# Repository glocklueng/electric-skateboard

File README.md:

electric-skateboard
===================

Hardware and a start to software for an electric skateboard. 

- v1 had some issues but was built and tested. 

- v2 is in progress. Board layout done, ordered from OSH Park.

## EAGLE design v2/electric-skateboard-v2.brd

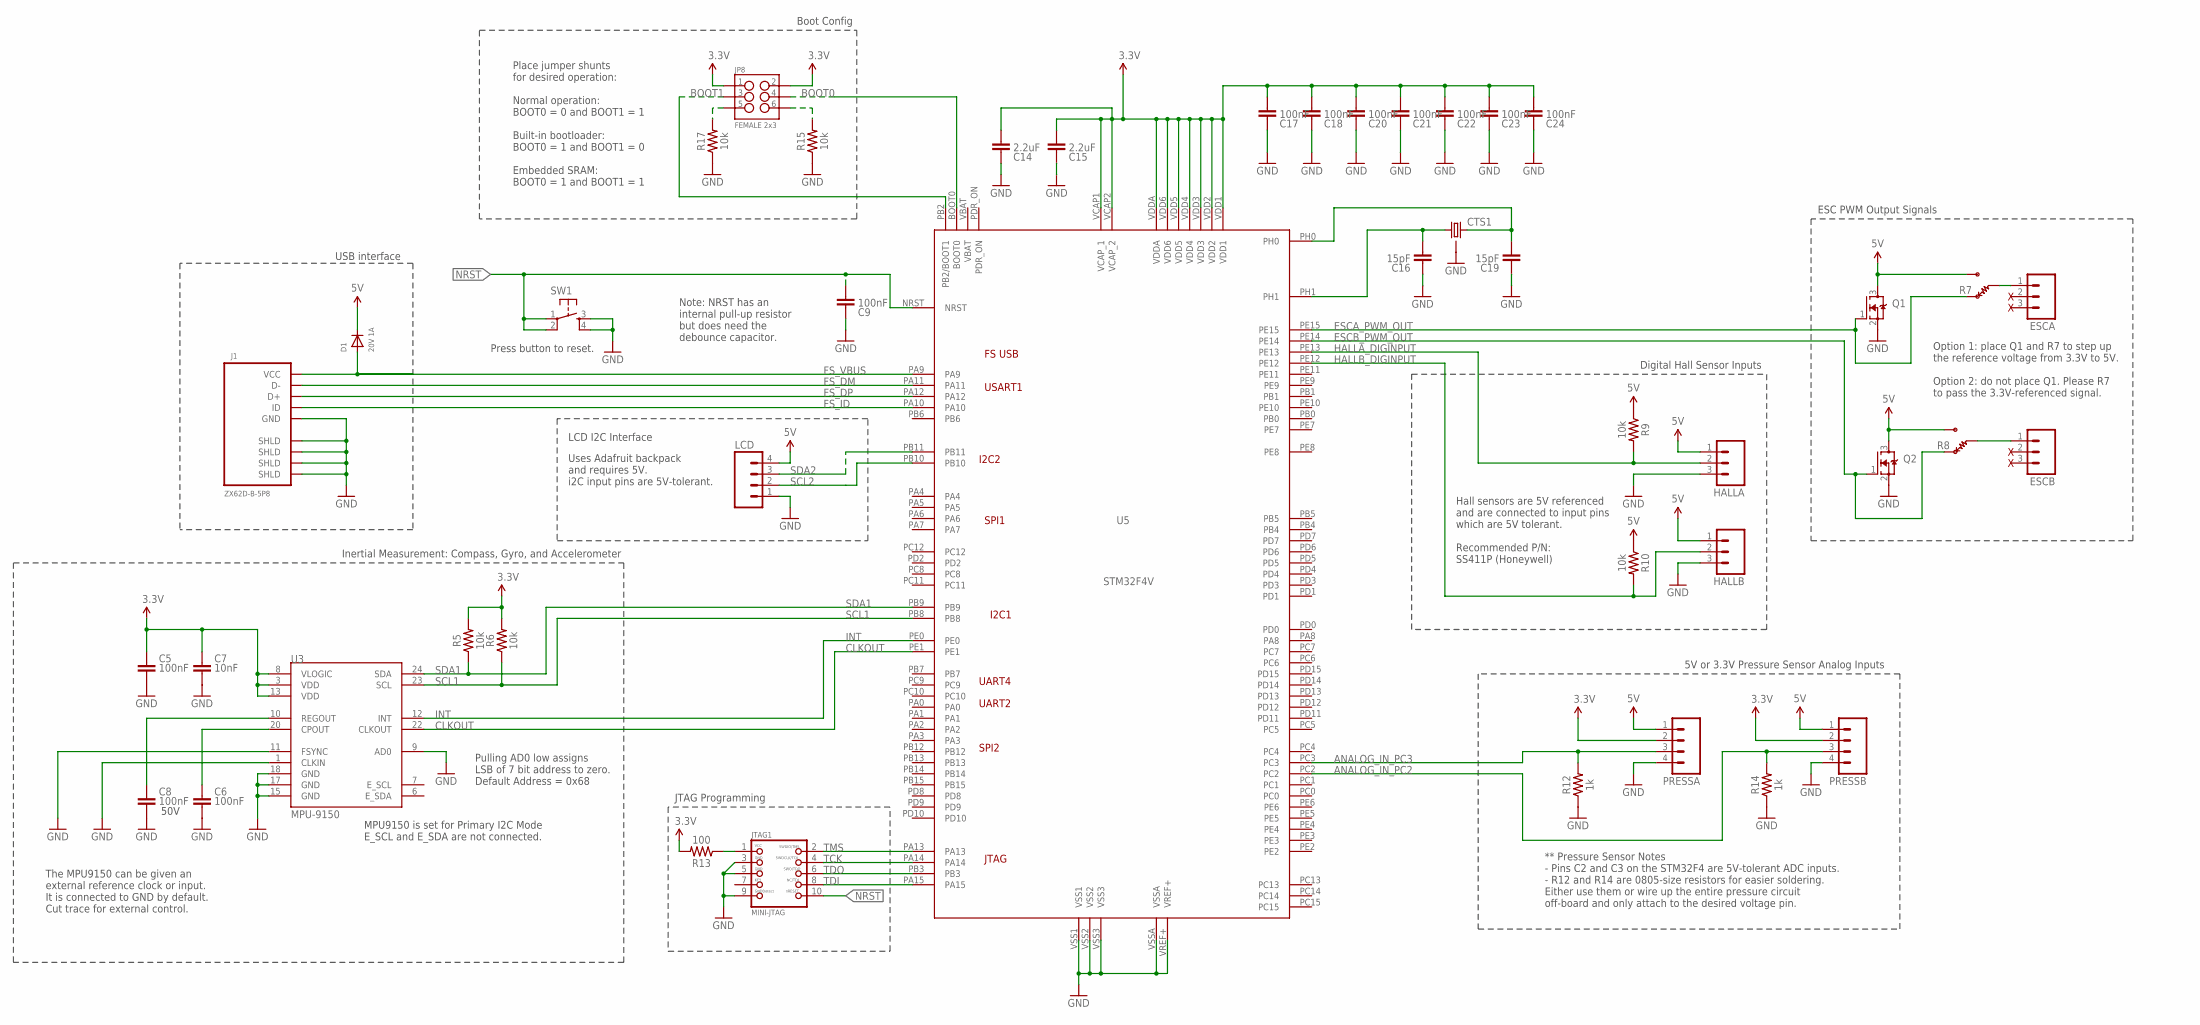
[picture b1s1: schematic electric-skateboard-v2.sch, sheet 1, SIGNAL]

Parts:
C5, C6, C8, C9, C17, C18, C20, C21, C22, C23, C24: 100nF; RLC-0402
C7: 10nF; RLC-0402
C14, C15: 2.2uF; RLC-0805
C16, C19: 15pF; RLC-0402
CTS1: CRYSTALCTS406; CTS406
D1: 20V 1A; SMADIODE
ESCA: M03LOCK_LONGPADS; 1X03_LOCK_LONGPADS
ESCB: M03LOCK_LONGPADS; 1X03_LOCK_LONGPADS
HALLA: M03LOCK_LONGPADS; 1X03_LOCK_LONGPADS
HALLB: M03LOCK_LONGPADS; 1X03_LOCK_LONGPADS
J1: ZX62D-B-5P8
JP8: FEMALE 2x3; 2X3
JTAG1: MINI-JTAG; MICROBUILDER_2X05_1.27MM_SMT
LCD: M04SCREW_LOCK; SCREWTERMINAL-3.5MM-4_LOCK
PRESSA: M04LOCK_LONGPADS; 1X04_LOCK_LONGPADS
PRESSB: M04LOCK_LONGPADS; 1X04_LOCK_LONGPADS
Q1, Q2: NTR4501N-D; SOT-23
R5, R6, R9, R10, R15, R17: 10k; RLC-0402
R7, R8: RES-OPTION; CAP-OPTION
R12, R14: 1k; RLC-0402
R13: 100; RLC-0402
SW1: TACTILE-SWITCH-PTH; TAC-SWITCH-PTH
U3: MPU-9150; QFN-24-NP
U5: STM32F4V; STM32F4_LQFP100

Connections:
3.3V: C5.1, C7.1, C14.2, C15.2, C17.2, C18.2, C20.2, C21.2, C22.2, C23.2, C24.2, JP8.1, JP8.2, PRESSA.2, PRESSB.2, R5.2, R6.2, R13.2, U3.3 (VDD), U3.8 (VLOGIC), U3.13 (VDD), U5.VCAP1 (VCAP_1), U5.VCAP2 (VCAP_2), U5.VDD1, U5.VDD2, U5.VDD3, U5.VDD4, U5.VDD5, U5.VDD6, U5.VDDA; also elsewhere on the board
5V: D1.C, HALLA.1, HALLB.1, LCD.4, PRESSA.1, PRESSB.1, Q1.3 (D), Q2.3 (D), R7.3, R8.3, R9.1, R10.1; also elsewhere on the board
ANALOG_IN_PC2: PRESSB.3, R14.2, U5.PC2
ANALOG_IN_PC3: PRESSA.3, R12.2, U5.PC3
BOOT0: JP8.4, U5.BOOT0
BOOT1: JP8.3, U5.PB2 (PB2/BOOT1)
CLKOUT: U3.22 (CLKOUT), U5.PE1
ESCA: ESCA.1, R7.2
ESCA_PWM_OUT: Q1.1 (G), R7.1, U5.PE15
ESCB: ESCB.1, R8.2
ESCB_PWM_OUT: Q2.1 (G), R8.1, U5.PE14
FS_DM: J1.P2 (D-), U5.PA11
FS_DP: J1.P3 (D+), U5.PA12
FS_ID: J1.P4 (ID), U5.PA10
FS_VBUS: D1.A, J1.P1 (VCC), U5.PA9
GND: C5.2, C6.2, C7.2, C8.2, C9.1, C14.1, C15.1, C16.1, C17.1, C18.1, C19.1, C20.1, C21.1, C22.1, C23.1, C24.1, CTS1.2 (GND), CTS1.4 (GND), HALLA.3, HALLB.3, J1.P5 (GND), J1.P$1 (SHLD), J1.P$2 (SHLD), J1.P$3 (SHLD), J1.P$4 (SHLD), JTAG1.3, JTAG1.5, JTAG1.9, LCD.1, PRESSA.4, PRESSB.4, Q1.2 (S), Q2.2 (S), R12.1, R14.1, R15.1, R17.1, SW1.3, SW1.4, U3.1 (CLKIN), U3.9 (AD0), U3.11 (FSYNC), U3.15 (GND), U3.17 (GND), U3.18 (GND), U5.VREF+, U5.VSS1, U5.VSS2, U5.VSS3, U5.VSSA; also elsewhere on the board
HALLA_DIGINPUT: HALLA.2, R9.2, U5.PE13
HALLB_DIGINPUT: HALLB.2, R10.2, U5.PE12
INT: U3.12 (INT), U5.PE0
unnamed: C6.1, U3.20 (CPOUT)
unnamed: JP8.6, R15.2
unnamed: JP8.5, R17.2
unnamed: C8.1, U3.10 (REGOUT)
unnamed: JTAG1.1, R13.1
NRST: C9.2, JTAG1.10, SW1.1, SW1.2, U5.NRST
OSC_IN1: C19.2, CTS1.3 (2), U5.PH0
OSC_OUT1: C16.2, CTS1.1, U5.PH1
SCL1: R6.1, U3.23 (SCL), U5.PB8
SCL2: LCD.2, U5.PB10
SDA1: R5.1, U3.24 (SDA), U5.PB9
SDA2: LCD.3, U5.PB11
TCK: JTAG1.4, U5.PA14
TDI: JTAG1.8, U5.PA15
TDO: JTAG1.6, U5.PB3
TMS: JTAG1.2, U5.PA13

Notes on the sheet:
50V
The MPU9150 can be given an external reference clock or input. It is connected to GND by default. Cut trace for external control.
Pulling AD0 low assigns LSB of 7 bit address to zero. Default Address = 0x68
MPU9150 is set for Primary I2C Mode E_SCL and E_SDA are not connected.
Option 1: place Q1 and R7 to step up the reference voltage from 3.3V to 5V. Option 2: do not place Q1. Please R7 to pass the 3.3V-referenced signal.
Hall sensors are 5V referenced and are connected to input pins which are 5V tolerant. Recommended P/N: SS411P (Honeywell)
** Pressure Sensor Notes - Pins C2 and C3 on the STM32F4 are 5V-tolerant ADC inputs. - R12 and R14 are 0805-size resistors for easier soldering. Either use them or wire up the entire pressure circuit off-board and only attach to the desired voltage pin.
ESC PWM Output Signals
Digital Hall Sensor Inputs
5V or 3.3V Pressure Sensor Analog Inputs
Inertial Measurement: Compass, Gyro, and Accelerometer
Note: NRST has an internal pull-up resistor but does need the debounce capacitor.
Place jumper shunts for desired operation: Normal operation: BOOT0 = 0 and BOOT1 = 1 Built-in bootloader: BOOT0 = 1 and BOOT1 = 0 Embedded SRAM: BOOT0 = 1 and BOOT1 = 1
Boot Config
Uses Adafruit backpack and requires 5V. i2C input pins are 5V-tolerant.
LCD I2C Interface
USB interface
JTAG Programming
Press button to reset.

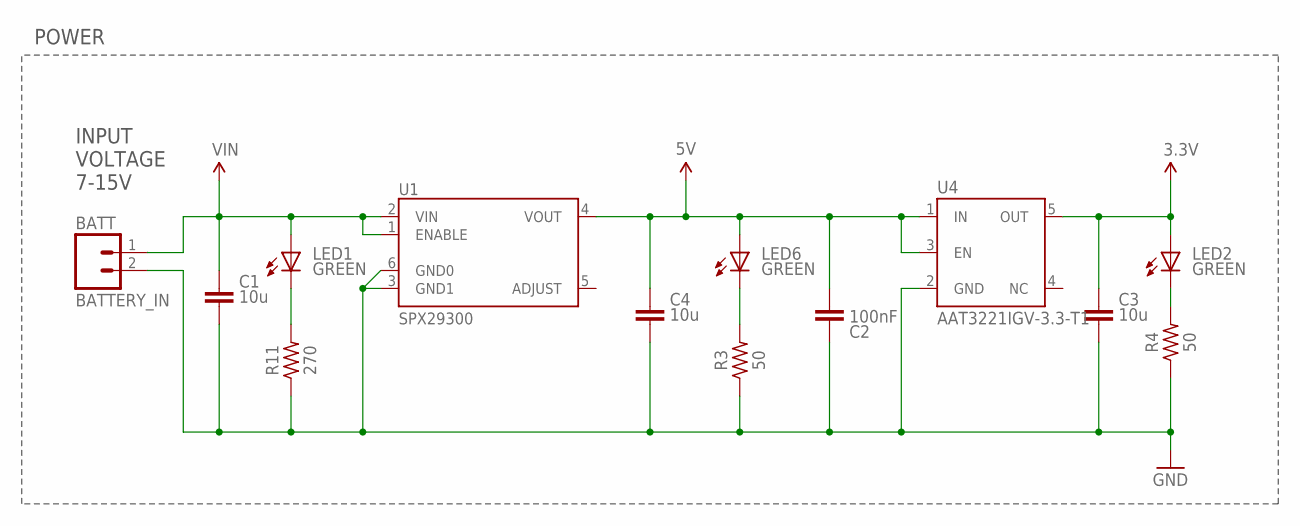
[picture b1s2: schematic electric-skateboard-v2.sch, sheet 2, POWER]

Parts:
BATTERY_IN: BATT; SCREWTERMINAL-5MM-2
C1, C3, C4: 10u; RLC-1210
C2: 100nF; RLC-0402
LED1, LED2, LED6: GREEN; LED0603
R3, R4: 50; RLC-0402
R11: 270; RLC-0402
U1: SPX29300; TO263-5
U4: AAT3221IGV-3.3-T1; SOT23-5

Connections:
3.3V: C3.1, LED2.A, U4.5 (OUT); also elsewhere on the board
5V: C2.2, C4.1, LED6.A, U1.4 (VOUT), U4.1 (IN), U4.3 (EN); also elsewhere on the board
GND: BATTERY_IN.2, C1.2, C2.1, C3.2, C4.2, R3.1, R4.1, R11.1, U1.3 (GND1), U1.6 (GND0), U4.2 (GND); also elsewhere on the board
unnamed: LED2.C, R4.2
unnamed: LED1.C, R11.2
unnamed: LED6.C, R3.2
VIN: BATTERY_IN.1, C1.1, LED1.A, U1.1 (ENABLE), U1.2 (VIN)

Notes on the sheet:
INPUT VOLTAGE 7-15V
POWER

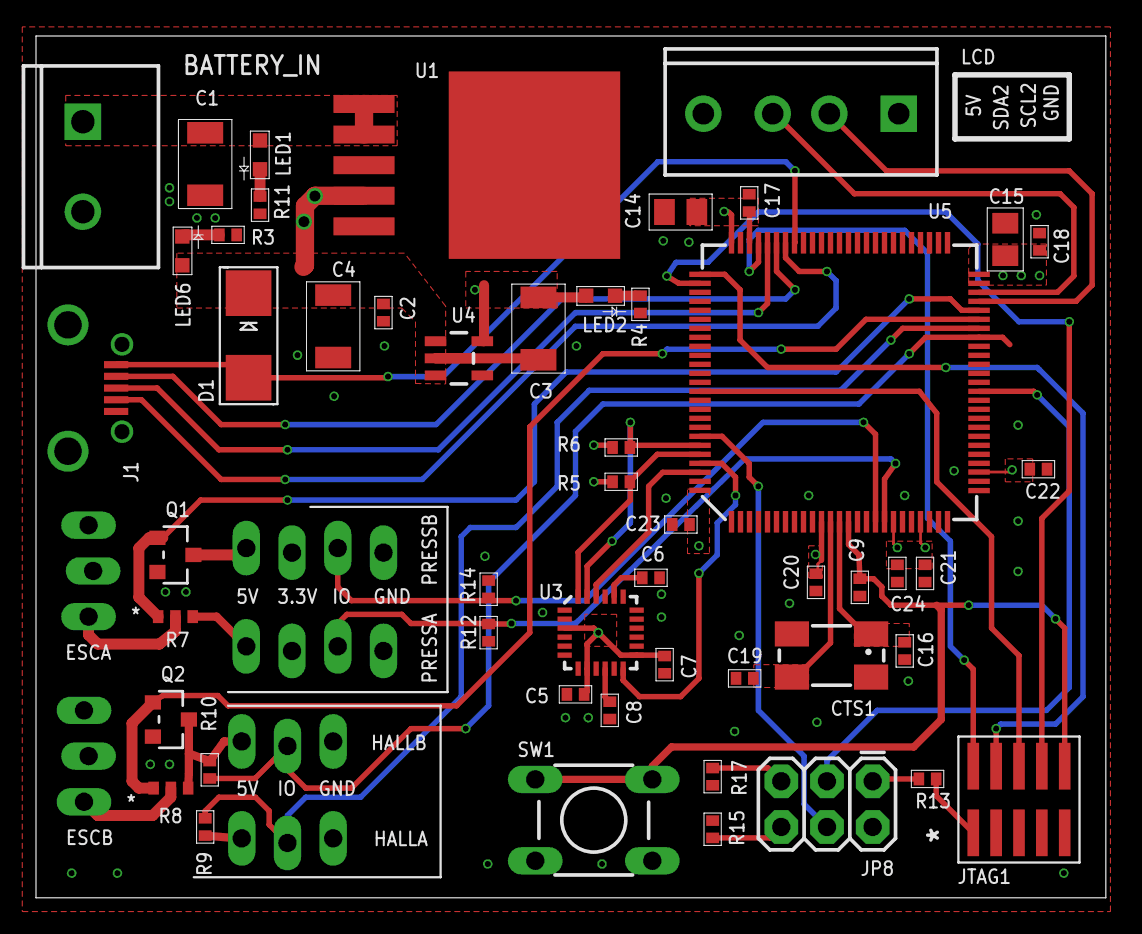
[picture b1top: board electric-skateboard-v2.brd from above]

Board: 4 copper layers, 59.4 x 47.9 mm, 57 parts (0 on the bottom side), 39 nets.

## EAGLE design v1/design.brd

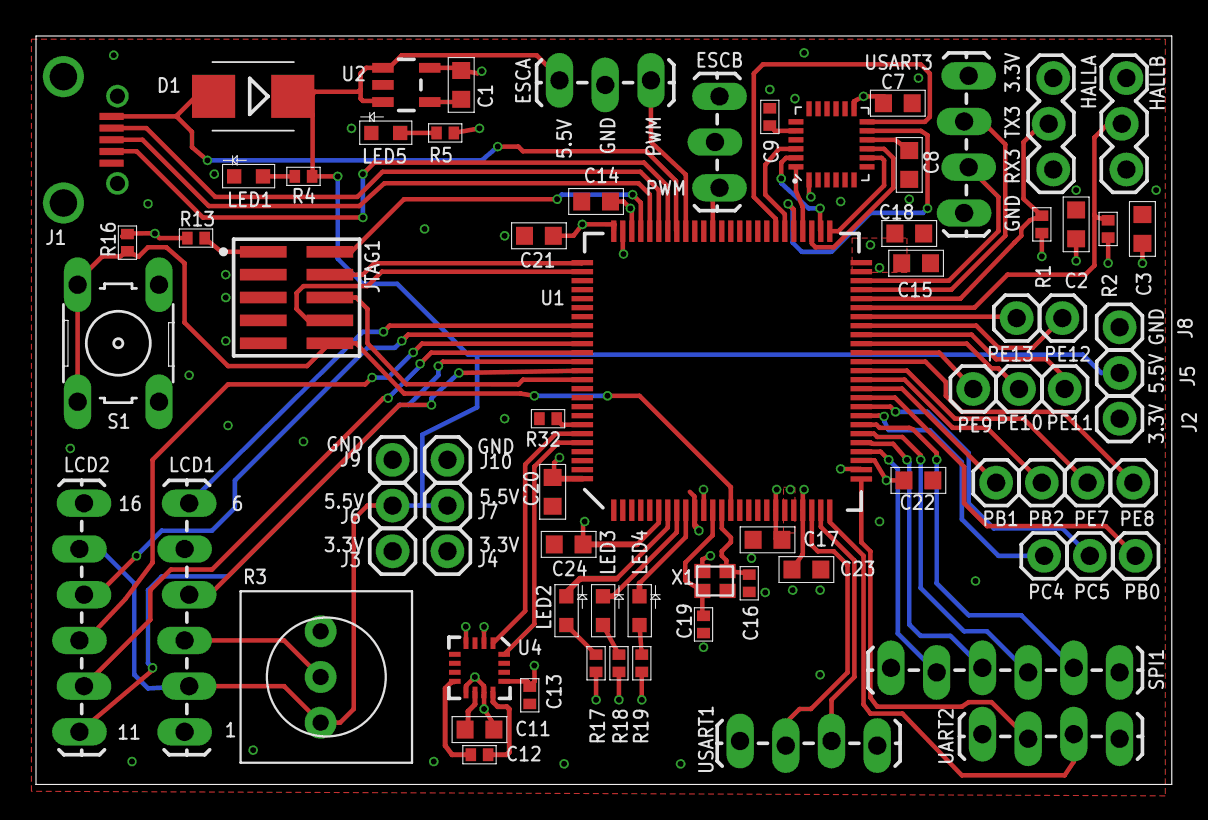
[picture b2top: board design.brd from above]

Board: 4 copper layers, 63.1 x 41.6 mm, 76 parts (0 on the bottom side), 72 nets.

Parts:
C1, C2, C3, C7, C8, C17, C18, C20, C21, C22, C23, C24: 100nF; RLC-0603
C9: 10nF; RLC-0402
C11: 4.7uF; RLC-0603
C12, C13: 220nF; RLC-0402
C14, C15: 2.2uF; RLC-0603
C16, C19: 15pF; RLC-0402
D1: 15V 1A; SMB
ESCA: ESCA; 1X03_LOCK_LONGPADS
ESCB: ESCB; 1X03_LOCK_LONGPADS
HALLA: HALLA; 1X03_LOCK
HALLB: HALLB; 1X03_LOCK
J1: ZX62D-B-5P8
J2, J3, J4, J5, J6, J7, J8, J9, J10: 1X01
JTAG1: MINI-JTAG; 2X05_1.27MM_SMT
LCD1: PINS1-6; 1X06_LOCK_LONGPADS
LCD2: PINS11-16; 1X06_LOCK_LONGPADS
LED1, LED5: GREEN; LED0603
LED2, LED3, LED4: BG1111C; LED0603
PB0, PB1, PB2: 1X01
PC4, PC5: 1X01
PE7, PE8, PE9, PE10, PE11, PE12, PE13: 1X01
R1, R2: 1.5k; RLC-0402
R3: TRIMPOT; TRIM-3386
R4: 499; RLC-0402
R5: 250; RLC-0402
R13: 100; RLC-0402
R16, R32: 10k; RLC-0402
R17, R18, R19: 49.9; RLC-0402
S1: RESET; B3F-10XX
SPI1: SPI1; 1X06_LOCK_LONGPADS
U1: STM32F4_STM32F4V_100PIN_FOXCAR; STM32F4_LQFP100
U2: MICLDO; SPARKFUN_SOT23-5
U3: MPU6000; QFN.24.4X4
U4: HMC5883LSMD; 16LPCC
UART2: UART2; 1X04_LOCK_LONGPADS
USART1: USART1; 1X04_LOCK_LONGPADS
USART3: USART3; 1X04_LOCK_LONGPADS
X1: 25MHz 8Y; 8Y_25MHZCRYSTAL_8Y

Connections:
3.3V: C1.2, C2.2, C3.2, C7.2, C13.1, C14.1, C15.1, C17.1, C18.1, C20.1, C21.1, C22.1, C23.1, C24.1, HALLA.3, HALLB.3, J2.1, J3.1, J4.1, R1.2, R2.2, R5.1, R13.2, R16.2, R17.1, R18.1, R19.1, SPI1.6, U1.VBAT, U1.VCAP1, U1.VCAP2, U1.VDD1, U1.VDD2, U1.VDD3, U1.VDD4, U1.VDD5, U1.VDD6, U1.VDDA, U2.5, U3.13, U4.2, U4.4, U4.13, UART2.4, USART1.4, USART3.4
5.5V: D1.C, ESCA.1, J5.1, J6.1, J7.1, LCD1.2, LCD2.5, R3.3, R4.1, U2.1, U2.3
BOOT0: R32.1, U1.BOOT0
ESCA_PWM: ESCA.3, U1.PA8
ESCB_PWM: ESCB.3, U1.PC7
FS_ID: J1.P4, U1.PA10
FS_N: J1.P2, U1.PA11
FS_P: J1.P3, U1.PA12
FS_VBUS: D1.A, J1.P1, U1.PA9
GND: C2.1, C3.1, C7.1, C8.1, C9.2, C11.1, C13.2, C14.2, C15.2, C16.1, C17.2, C18.2, C19.1, C20.2, C21.2, C22.2, C23.2, C24.2, ESCA.2, HALLA.1, HALLB.1, J1.P5, J1.P$1, J1.P$2, J1.P$3, J1.P$4, J8.1, J9.1, J10.1, JTAG1.3, JTAG1.5, JTAG1.9, LCD1.1, LCD1.5, LCD2.6, LED1.C, LED5.C, R3.1, R32.2, S1.3, S1.4, SPI1.1, U1.VREF+, U1.VSS1, U1.VSS2, U1.VSS3, U1.VSSA, U2.2, U3.1, U3.18, U4.9, U4.11, UART2.1, USART1.1, USART3.1, X1.2, X1.4
HALLAOUT: HALLA.2, R1.1, U1.PE15
HALLBOUT: HALLB.2, R2.1, U1.PE14
IMU_CLKOUT: U1.PD9, U3.22
IMU_FSYNC: U1.PD8, U3.11
IMU_INT: U1.PD10, U3.12
LCD_DATA4: LCD2.1, U1.PD6
LCD_DATA5: LCD2.2, U1.PD5
LCD_DATA6: LCD2.3, U1.PD4
LCD_DATA7: LCD2.4, U1.PD3
LCD_EN: LCD1.6, U1.PD2
LCD_RS: LCD1.4, U1.PD7
LCD_V0: LCD1.3, R3.2
LED_B: LED4.C, U1.PC15
LED_G: LED3.C, U1.PC14
LED_R: LED2.C, U1.PC13
unnamed: LED5.A, R5.2
unnamed: LED1.A, R4.2
unnamed: C1.1, U2.4
unnamed: C12.2, U4.12
unnamed: LED2.A, R17.2
unnamed: LED3.A, R18.2
unnamed: LED4.A, R19.2
unnamed: C12.1, U4.8
unnamed: C11.2, U4.10
unnamed: C9.1, U3.20
unnamed: JTAG1.1, R13.1
NRST: JTAG1.10, R16.1, S1.1, S1.2, U1.NRST
OSC_IN1: C19.2, U1.PH0, X1.1
OSC_OUT1: C16.2, U1.PH1, X1.3
PB0: PB0.1, U1.PB0
PB1: PB1.1, U1.PB1
PB2: PB2.1, U1.PB2
PC4: PC4.1, U1.PC4
PC5: PC5.1, U1.PC5
PE7: PE7.1, U1.PE7
PE8: PE8.1, U1.PE8
PE9: PE9.1, U1.PE9
PE10: PE10.1, U1.PE10
PE11: PE11.1, U1.PE11
PE12: PE12.1, U1.PE12
PE13: PE13.1, U1.PE13
REGOUT: C8.2, U3.10
RX1: U1.PA1, USART1.2
RX2: U1.PA3, UART2.2
RX3: U1.PB11, USART3.2
SCL1: U1.PB8, U4.1
SDA1: U1.PB9, U4.16
SPI1_MISO: SPI1.3, U1.PA6
SPI1_MOSI: SPI1.2, U1.PA7
SPI1_NSS: SPI1.5, U1.PA4
SPI1_SCK: SPI1.4, U1.PA5
SPI2_CS: U1.PB12, U3.8
SPI2_MISO: U1.PB14, U3.9
SPI2_MOSI: U1.PB15, U3.24
SPI2_SCK: U1.PB13, U3.23
TCK: JTAG1.4, U1.PA14
TDI: JTAG1.8, U1.PA15
TDO: JTAG1.6, U1.PB3
TMS: JTAG1.2, U1.PA13
TX1: U1.PA0, USART1.3
TX2: U1.PA2, UART2.3
TX3: U1.PB10, USART3.3

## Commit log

2014-07-18 It's a block diagram\!
2015-01-09 Adding salvaged board file, lost the schematic file.
2015-05-12 Fixing up the whole repo. Added schematic for v2. Needs layout.
2015-05-13 In theory I could ship this layout but I'm ashamed of it. It's gross.
2015-05-16 Needs final review but otherwise layout is done.
2015-05-16 Shipping it.
2015-05-16 Update status of v2: ordered board from OSH Park.
2015-05-18 Added button. Changed LDO.
2015-05-24 Added final v2 of eskate and ordered from OSHPark.

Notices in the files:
parts and their libraries:
SparkFun-Connectors: Licensing: CC v3.0 Share-Alike You are welcome to use this library for commercial purposes.
SparkFun-DigitalIC: Licensing: Creative Commons ShareAlike 4.0 International - https://creativecommons.org/licenses/by-sa/4.0
